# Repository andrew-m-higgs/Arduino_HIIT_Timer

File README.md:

# Arduino_HIIT_Timer

This simple Arduino sketch performs as follows:
* When switch on the screen is drawn. Press the buttun to begin.
* A period of Warm Up begins (time set in code. Deafault is 180s)
* This is followed by a number of circuits (default is 4). for each circuit:
  * Each execise is run (default is 7). An exercise consists of 30s work out.
  * This is followed by 15s of rest after each exercise.
* Each circuit is followed by a 60s break.
* Then comes the Warm Down. This is also 180s.

This project aims to make a useful yet uncomplicated device to assist with staying fot at home.

## Arduino Version
The Arduino version requires:
* An Arduino.
* A switch
* A buzzer or and LED
* A screen (code uses a 20x4 LCD)
* A 10K variable resistor (if using the screen)

## The Standalone Version
The Standalone version requires:
* An ATMega328P chip (will work with other version as long as there are enough free pins)
* 16Mhz crystal
* 2 22pF capacitors
* 1x 10K resistor
* A switch
* A buzzer or and LED
* A screen (code uses a 20x4 LCD)
* A 10K variable resistor (if using the screen)

In the Drawings folder of this repository you will find Breadboard diagram from Fritzing (and the Fritzing project). I have complete the Breadboard but not the schematic or PCB. I have also included some as yet unfinished KiCAD drawings of both version mention above.

Hope you have fun building this.

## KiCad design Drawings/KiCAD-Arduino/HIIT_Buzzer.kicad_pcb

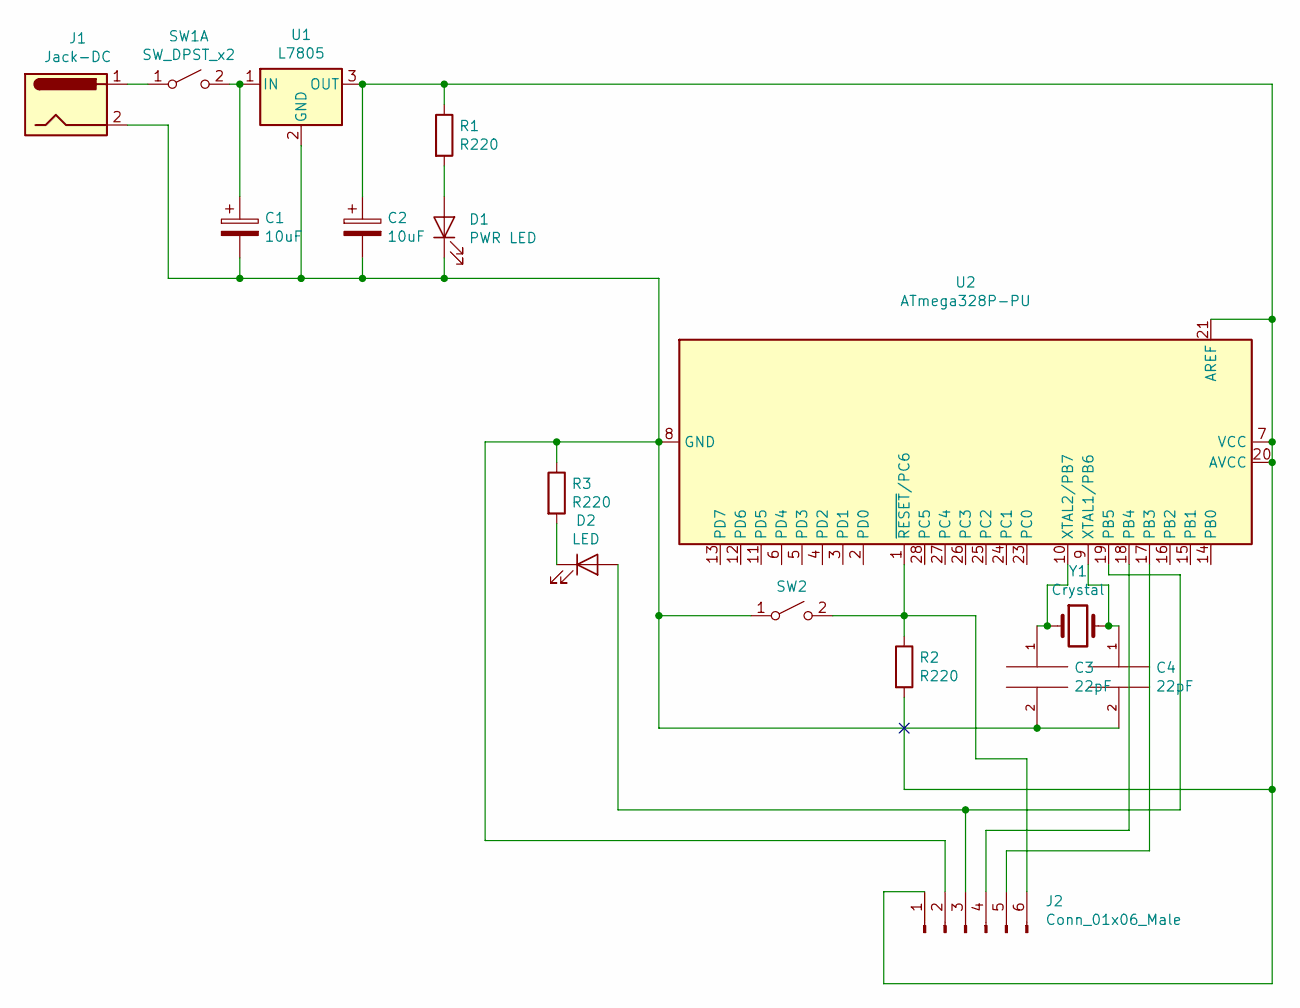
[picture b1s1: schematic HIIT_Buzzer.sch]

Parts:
C1, C2: 10uF; CP_Radial_D5.0mm_P2.50mm
C3, C4: 22pF; C_Disc_D3.0mm_W2.0mm_P2.50mm
D1: PWR LED; LED_D3.0mm
D2: LED; LED_D3.0mm
J1: Jack-DC; BarrelJack_Horizontal
J2: Conn_01x06_Male; PinHeader_1x06_P2.54mm_Vertical
R1, R2, R3: R220; R_Axial_DIN0207_L6.3mm_D2.5mm_P7.62mm_Horizontal
SW1: SW_DPST_x2; SW_PUSH_6mm_H4.3mm
SW2: SW_RESET; SW_PUSH_6mm_H4.3mm
U1: L7805; TO-220-3_Vertical
U2: ATmega328P-PU; DIP-28_W7.62mm
Y1: Crystal; Crystal_HC49-U_Vertical

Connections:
unnamed: C1.1, SW1.2 (B), U1.1 (IN)
unnamed: C1.2, C2.2, C3.2, C4.2, D1.1 (K), J1.2, J2.2, R3.1, SW2.1 (A), U1.2 (GND), U2.8 (GND), U2.22 (GND)
unnamed: C2.1, J2.1, R1.1, R2.2, U1.3 (OUT), U2.7 (VCC), U2.20 (AVCC), U2.21 (AREF)
unnamed: C3.1, U2.10 (XTAL2/PB7), Y1.1
unnamed: C4.1, U2.9 (XTAL1/PB6), Y1.2
unnamed: D1.2 (A), R1.2
unnamed: D2.1 (K), R3.2
unnamed: D2.2 (A), J2.3, U2.19 (PB5)
unnamed: J1.1, SW1.1 (A)
unnamed: J2.4, U2.18 (PB4)
unnamed: J2.5, U2.17 (PB3)
unnamed: J2.6, R2.1, SW2.2 (B), U2.1 (~RESET~/PC6)

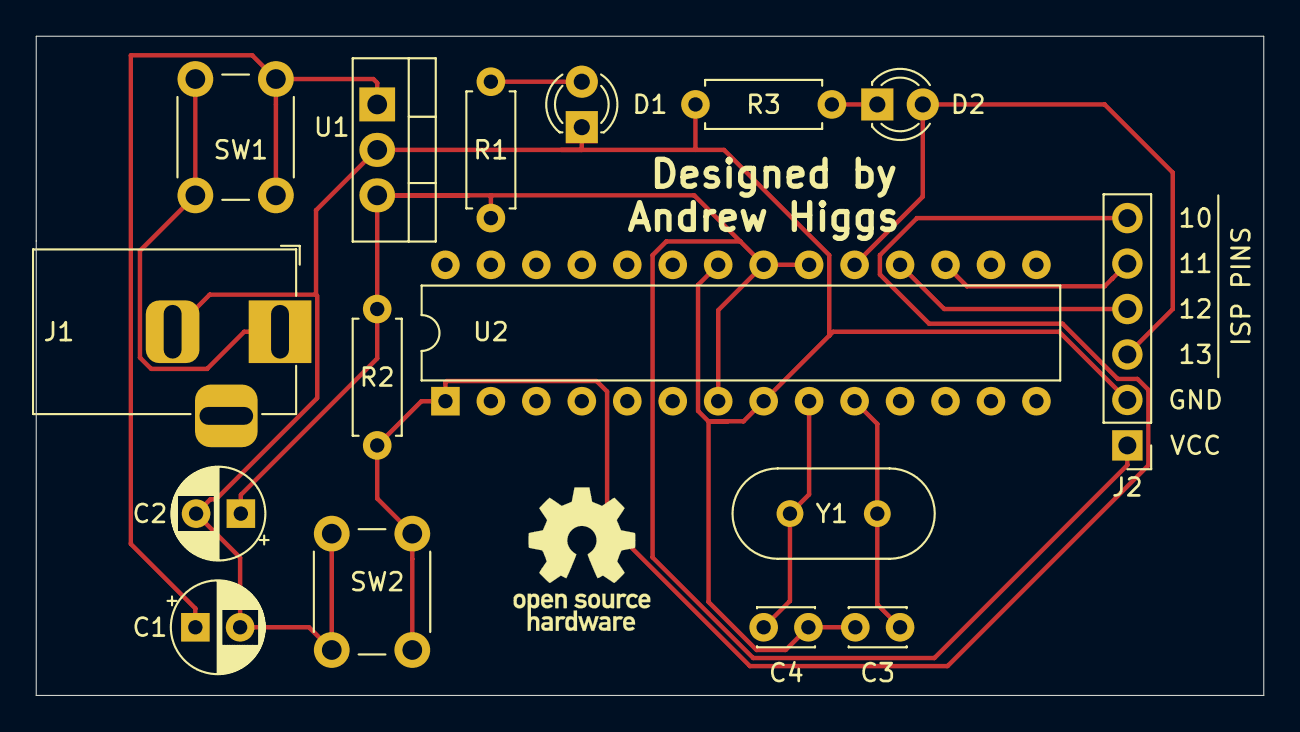
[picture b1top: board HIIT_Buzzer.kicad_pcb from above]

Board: 2 copper layers, 68.6 x 36.8 mm, 16 parts (0 on the bottom side), 12 nets.
